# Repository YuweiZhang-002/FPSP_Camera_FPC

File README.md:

# FPSP_Camera_FPC

This repo contains FPC schematics of the newly developed FPSP camera project on an FPC board, aiming for super-high-speed parallel image processing.

## Repository Structure
| Directory | Use |
| --------- | --- |
| archive_old/ | Archived initial design (**not working**) |
| custom_fp/ | Footprint from external libraries |
| docs/ | Documentation gathered from external sources |
| camera_bringup_min/ | RP2350 firmware: OV5640 driver and PIO heartbeat |

## TODO
- [x] RP2350 Power Supply Layout
- [ ] Add Proper Power Sequencing
- [ ] Source RP2354 A4
- [ ] Source B2B Connector
- [x] B2B Connector Pinout + Layout
- [x] HSTX Layout

## 12/12/2025 PCB ordering notes

- order FR-4 board with SMT assembly, run thru **functionality tests**
- order FPC without SMT assembly, test the **FPC characteristics and stiffener position**
- RP2345A and ICM45686 IMU ordered separately to test the functionality. Once it passes the prototype test, order at JLCPCB via **global sourcing** and prep for next assembly

### TODO
 - [x] Place JLCPCB order
 - [ ] functionality test, FR4 prototype
 - [ ] functionality test, FPC stiffener position
------ 
 - [ ] sourcing RP2345A
 - [ ] sourcing ICM45686
 - [ ] sourcing board-to-board connectors from Molex 

## Firmware

Camera (OV5640) bring-up firmware for the Raspberry Pi RP2350 (pico2 board).

### Build

Standard Raspberry Pi Pico SDK CMake project. Open it with the
**Raspberry Pi Pico** VS Code extension, or configure manually:

```sh
cmake -B build -G Ninja
cmake --build build
```

Target platform: `rp2350` / board `pico2` (set in `CMakeLists.txt`).

Key files: `main.c`, `camera_bringup_min/` (OV5640 driver + PIO heartbeat),
`CMakeLists.txt`, `pico_sdk_import.cmake`.

### Firmware dependencies

Depends on the [Raspberry Pi Pico SDK](https://github.com/raspberrypi/pico-sdk)
(v2.2.0), licensed under BSD-3-Clause. The SDK is **not** included in this
repository — install it via the Pico VS Code extension or set the
`PICO_SDK_PATH` environment variable to your local SDK checkout.

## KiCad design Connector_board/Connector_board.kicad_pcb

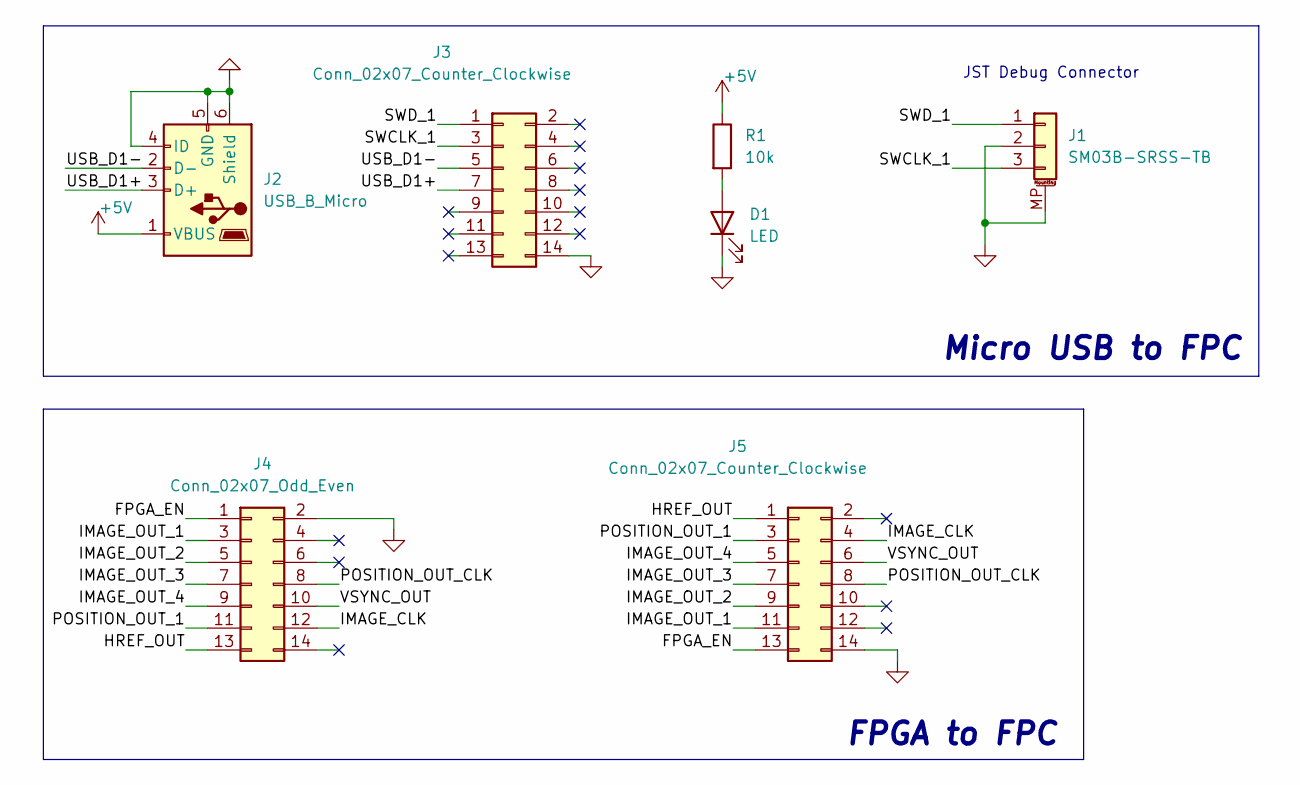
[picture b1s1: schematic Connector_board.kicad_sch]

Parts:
D1: LED; D_0603_1608Metric
J1: SM03B-SRSS-TB; JST_SH_SM03B-SRSS-TB_1x03-1MP_P1.00mm_Horizontal
J2: USB_B_Micro; USB_Micro-B_Molex_47346-0001
J3, J5: Conn_02x07_Counter_Clockwise; Molex_SlimStack_502430-1410_2x07_P0.40mm_Vertical
J4: Conn_02x07_Odd_Even; PinHeader_2x07_P2.54mm_Vertical
R1: 10k; R_0603_1608Metric_Pad0.98x0.95mm_HandSolder

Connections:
+5V: J2.1 (VBUS), R1.1
/FPGA_EN: J4.1, J5.13
/HREF_OUT: J4.13, J5.1
/IMAGE_CLK: J4.12, J5.4
/IMAGE_OUT_1: J4.3, J5.11
/IMAGE_OUT_2: J4.5, J5.9
/IMAGE_OUT_3: J4.7, J5.7
/IMAGE_OUT_4: J4.9, J5.5
/POSITION_OUT_1: J4.11, J5.3
/POSITION_OUT_CLK: J4.8, J5.8
/SWCLK_1: J1.3, J3.3
/SWD_1: J1.1, J3.1
/USB_D1+: J2.3 (D+), J3.7
/USB_D1-: J2.2 (D-), J3.5
/VSYNC_OUT: J4.10, J5.6
GND: D1.1 (K), J1.2, J1.MP (MountPin), J2.4 (ID), J2.5 (GND), J2.6 (Shield), J3.14, J3.15, J4.2, J5.14, J5.15
unnamed: D1.2 (A), R1.2

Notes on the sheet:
FPGA to FPC
Micro USB to FPC
JST Debug Connector

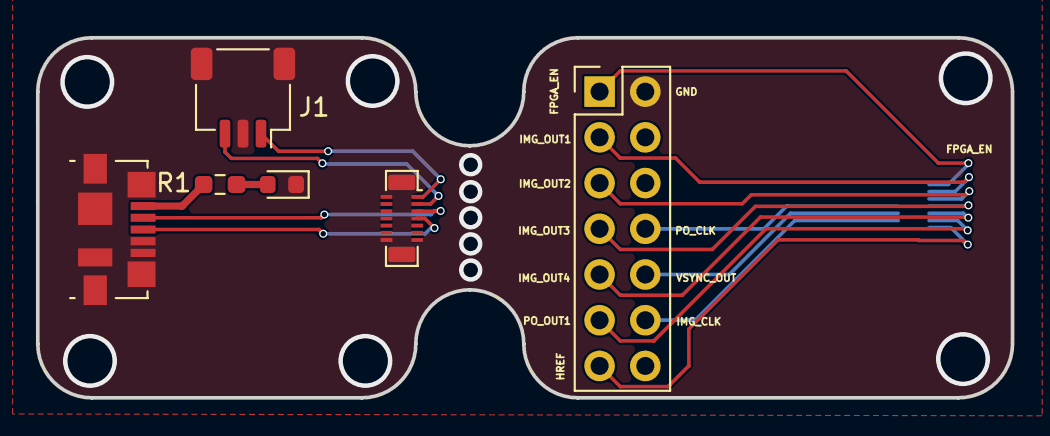
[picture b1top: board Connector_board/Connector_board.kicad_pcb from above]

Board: 2 copper layers, 54.2 x 20.0 mm, 7 parts (1 on the bottom side), 17 nets.

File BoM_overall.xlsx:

Part Name | Series Number / Description | Quantity | Source | Unit Price (GBP) | Order Code / Mouser No | Link
USB_B_Micro | USB_Micro-B_Molex_47346-0001 | 5 | Farnell | 1.2 | 1568026 | https://uk.farnell.com/molex/47346-0001/micro-usb-conn-2-0-t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
Conn_02x04_Counter_Clockwise | Molex_SlimStack_502430-0822_2x04_P0.40mm_Vertical | 5 | Mouser | 0.52 | 538-50243-00822 | https://www.mouser.co.uk/ProductDetail/Molex/502430-0822?qs=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
Conn_02x07_Counter_Clockwise | Molex_SlimStack_502430-1430_2x07_P0.40mm_Vertical | 10 | Farnell | 0.46500000000000002 | 3911710 | https://uk.farnell.com/molex/502430-1430/mezzanine-conn-hdr-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
Conn_02x04_Counter_Clockwise | Molex_SlimStack_502426-0812_2x04_P0.40mm_Vertical | 5 | Mouser | 0.55000000000000004 | 538-50242-60812 | https://www.mouser.co.uk/ProductDetail/Molex/502426-0812?qs=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
Conn_02x07_Counter_Clockwise | Molex_SlimStack_502426-1430_2x07_P0.40mm_Vertical | 10 | Farnell | 0.86799999999999999 | 3500584 | https://uk.farnell.com/molex/502426-1430/mezzanine-conn-rcpt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
SM03B-SRSS-TB | JST_SH_SM03B-SRSS-TB_1x03-1MP_P1.00mm_Horizontal | 5 | Farnell | 0.52 | 1679118 | https://uk.farnell.com/jst-japan-solderless-terminals/sm03b-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
IMU | ICM-45686 | 5 | Farnell | 7.8840000000000003 | 4572492 | https://uk.farnell.com/tdk/icm-45686/mems-module-6-axis-1-71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
LDO | TLV73315PDRV | 5 | Mouser | 0.44 | 595-TLV73315PQDRVRQ1 | https://www.mouser.co.uk/ProductDetail/Texas-Instruments/TLV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
MCU | RP2354A | 5 | Mouser | 0.751 | 358-SC151113 | https://www.mouser.co.uk/ProductDetail/Raspberry-Pi/SC151113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
Mems | SiT8008BI-13-33E-12.000000G | 5 | Mouser | 0.72099999999999997 | 788-8008BI1333E12G | https://www.mouser.co.uk/ProductDetail/SiTime/SiT8008BI-13-3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
FPC socket | molex 52435-2471 | 10 | Farnell | 2.3519999999999999 | 2396220 | https://uk.farnell.com/molex/52435-2471/connector-ffc-fpc-24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
Camera | OV5640 - 24pin fpc | 2 | Ali | N/A | N/A | https://www.aliexpress.com/p/tesla-landing/index.html?UTABTe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
2.54mm pin header: from UCL
0603 R&C: from UCL

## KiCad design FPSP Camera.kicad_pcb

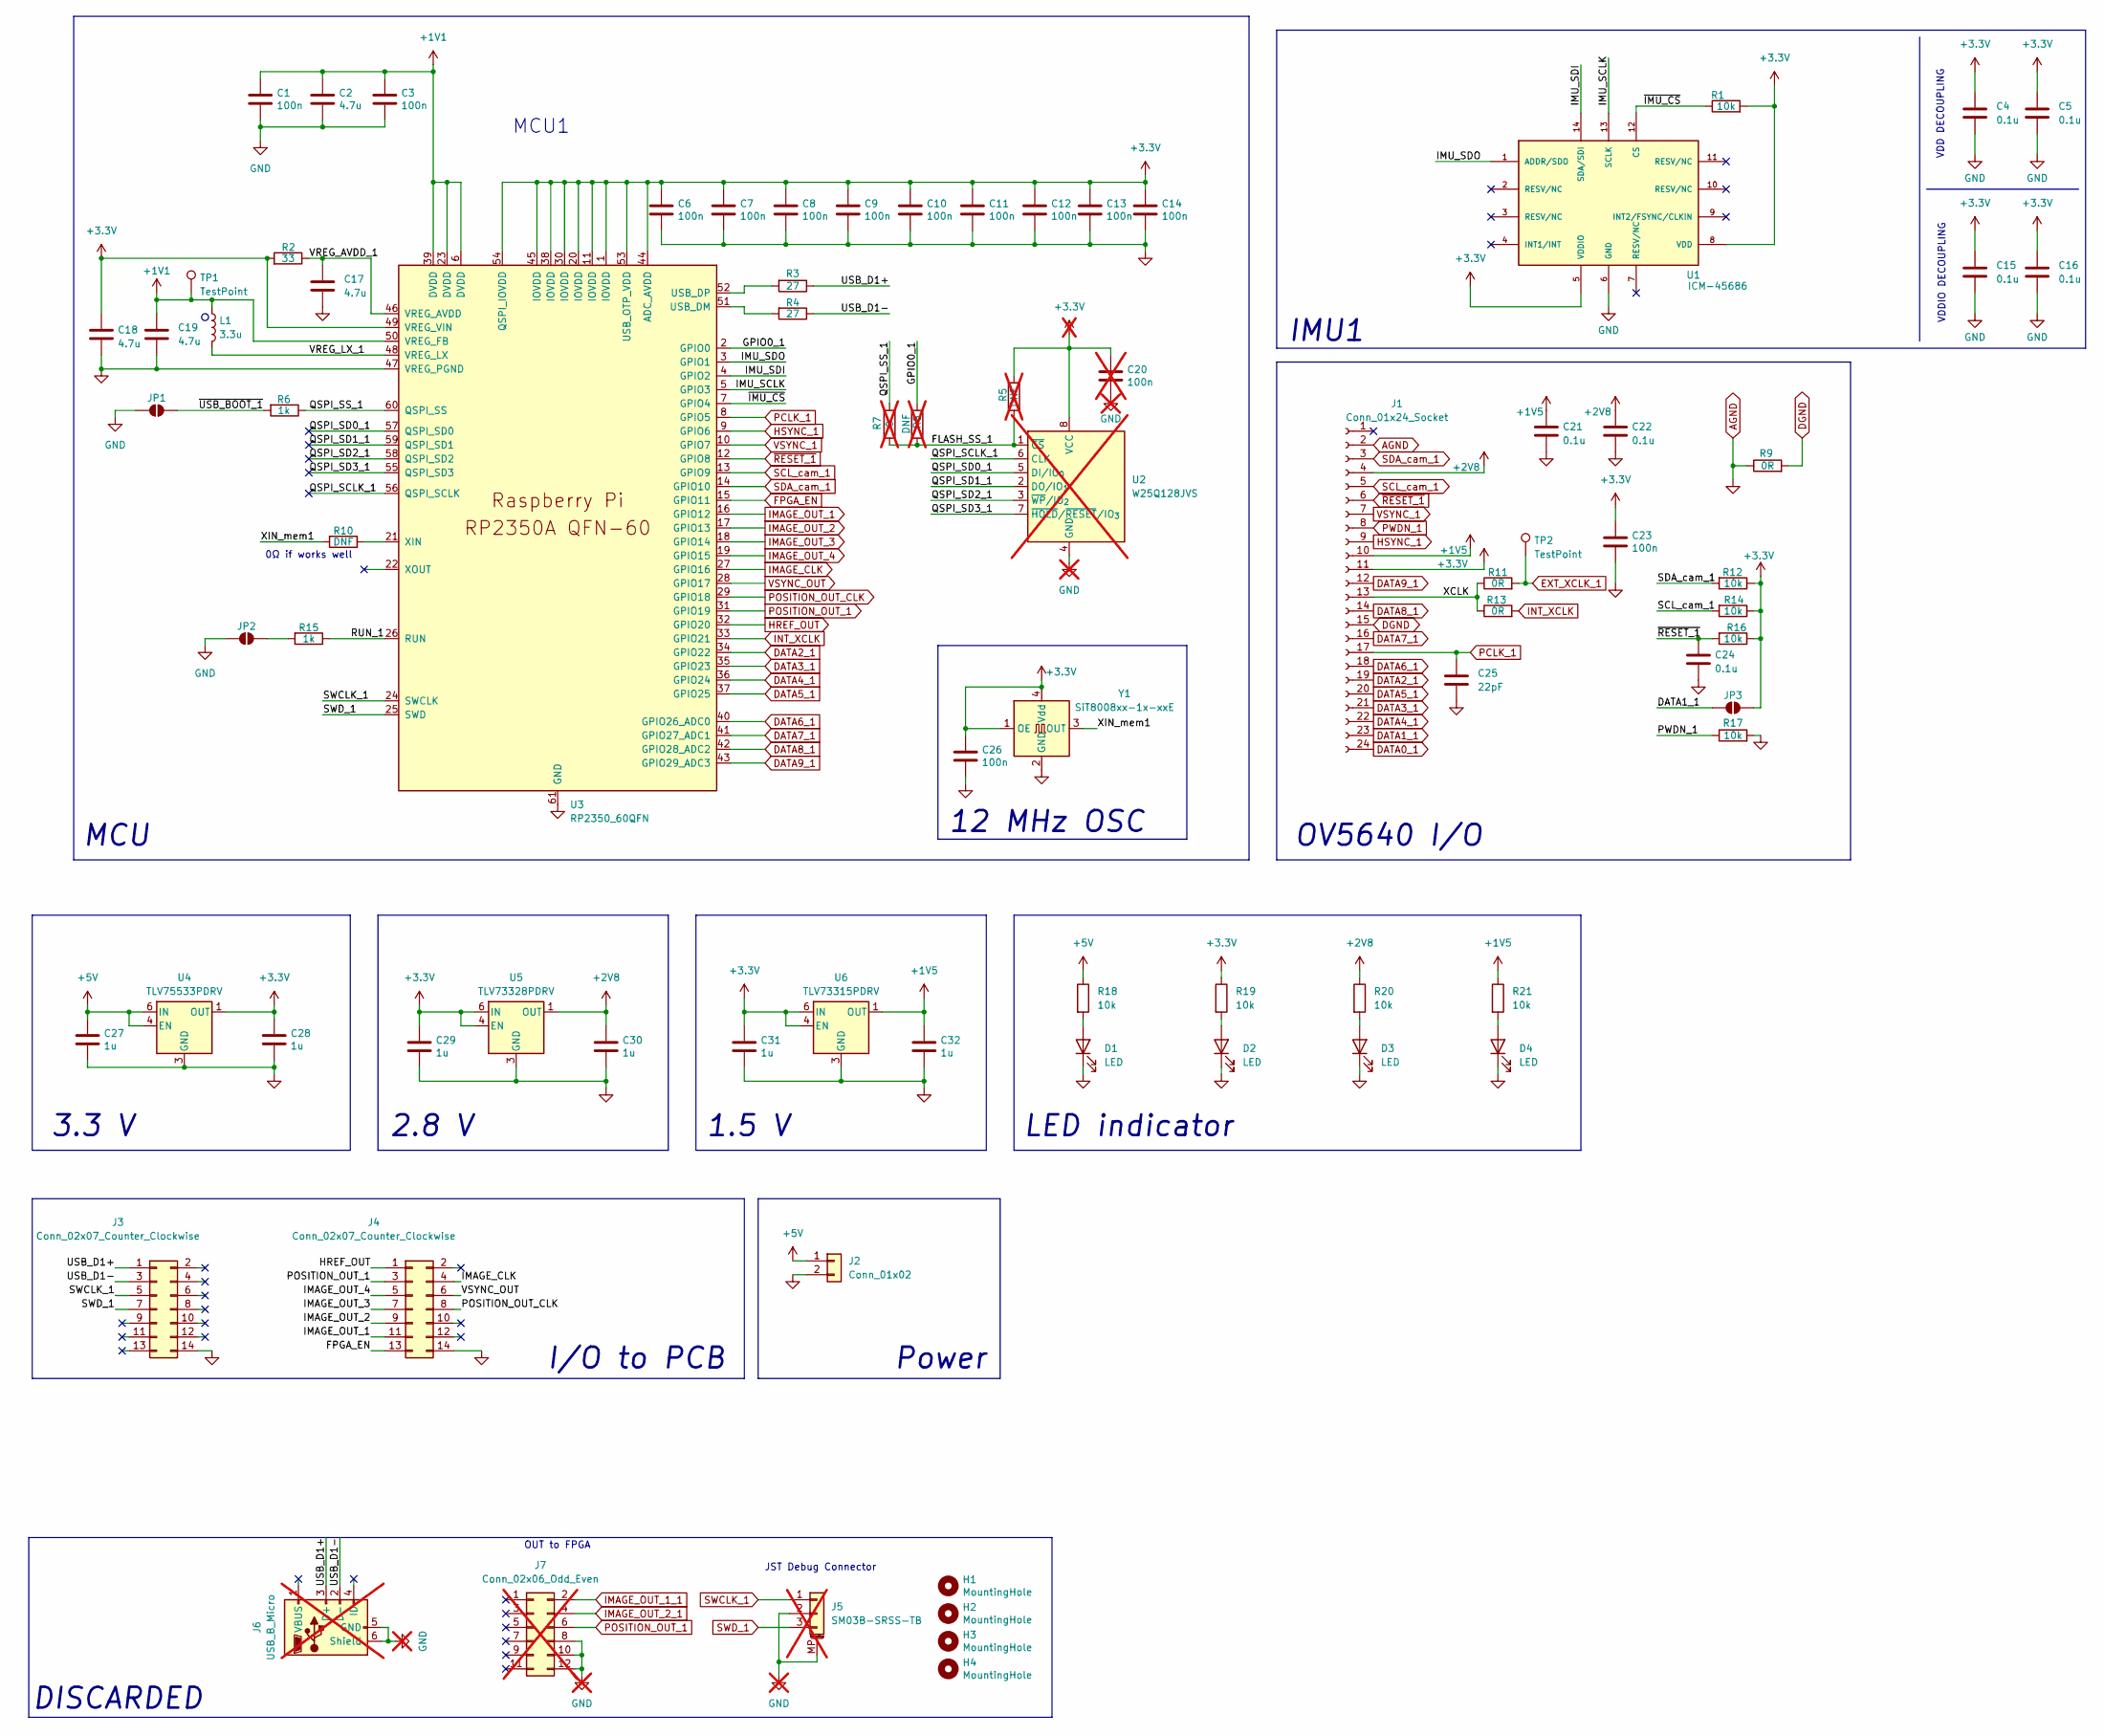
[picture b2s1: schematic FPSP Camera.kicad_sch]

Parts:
C1, C3, C6, C7, C8, C9, C10, C11, C12, C13, C14, C23, C26: 100n; C_0402_1005Metric
C2, C17, C18, C19: 4.7u; C_0402_1005Metric
C4, C5, C15, C16, C21, C22, C24: 0.1u; C_0402_1005Metric
C20: 100n; C_0603_1608Metric_Pad1.08x0.95mm_HandSolder; not fitted
C25: 22pF; C_0402_1005Metric
C27, C28, C29, C30, C31, C32: 1u; C_0402_1005Metric
D1, D2, D3, D4: LED; D_0603_1608Metric
H1, H2, H3, H4: MountingHole; MountingHole_2.7mm_M2.5
J1: Conn_01x24_Socket; MOLEX_52435-2471
J2: Conn_01x02; PinHeader_1x02_P2.54mm_Vertical
J3, J4: Conn_02x07_Counter_Clockwise; Molex_SlimStack_502426-1410_2x07_P0.40mm_Vertical
J5: SM03B-SRSS-TB; JST_SH_SM03B-SRSS-TB_1x03-1MP_P1.00mm_Horizontal; not fitted
J6: USB_B_Micro; USB_Micro-B_Amphenol_10103594-0001LF_Horizontal_modified; not fitted
J7: Conn_02x06_Odd_Even; PinHeader_2x06_P2.54mm_Vertical; not fitted
JP1, JP2, JP3: SolderJumper_2_Open; SolderJumper-2_P1.3mm_Open_RoundedPad1.0x1.5mm
L1: 3.3u; L_pol_2016
R1: 10k; R_0402_1005Metric_Pad0.72x0.64mm_HandSolder
R2: 33; R_0402_1005Metric
R3, R4: 27; R_0402_1005Metric
R5, R8: DNF; R_0603_1608Metric_Pad0.98x0.95mm_HandSolder; not fitted
R6, R15: 1k; R_0402_1005Metric
R7: 0; R_0603_1608Metric_Pad0.98x0.95mm_HandSolder; not fitted
R9, R11, R13: 0R; R_0402_1005Metric
R10: DNF; R_0402_1005Metric
R12, R14, R16, R17, R18, R19, R20, R21: 10k; R_0402_1005Metric
TP1, TP2: TestPoint; TestPoint_Pad_D1.0mm
U1: ICM-45686; IC_ICM-45686; PARTREV 0.2
U2: W25Q128JVS; SOIC-8_5.3x5.3mm_P1.27mm; not fitted
U3: RP2350_60QFN; RP2350-QFN-60-1EP_7x7_P0.4mm_EP3.4x3.4mm_ThermalVias
U4: TLV75533PDRV; WSON-6-1EP_2x2mm_P0.65mm_EP1x1.6mm
U5: TLV73328PDRV; WSON-6-1EP_2x2mm_P0.65mm_EP1x1.6mm
U6: TLV73315PDRV; WSON-6-1EP_2x2mm_P0.65mm_EP1x1.6mm
Y1: SiT8008xx-1x-xxE; Oscillator_SMD_SiT_PQFN-4Pin_2.5x2.0mm

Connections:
+1V1: C1.1, C2.1, C3.1, C19.1, L1.1, TP1.1 (1_1), U3.6 (DVDD), U3.23 (DVDD), U3.39 (DVDD), U3.50 (VREG_FB)
+1V5: C21.1, C32.1, J1.10, R21.1, U6.1 (OUT)
+2V8: C22.1, C30.1, J1.4, R20.1, U5.1 (OUT)
+3.3V: C4.1, C5.1, C6.1, C7.1, C8.1, C9.1, C10.1, C11.1, C12.1, C13.1, C14.1, C15.1, C16.1, C18.1, C20.1, C23.1, C26.1, C28.1, C29.1, C31.1, J1.11, JP3.2 (B), R1.2, R2.2, R5.1, R12.1, R14.1, R16.1, R19.1, U1.5 (VDDIO), U1.8 (VDD), U2.8 (VCC), U3.1 (IOVDD), U3.11 (IOVDD), U3.20 (IOVDD), U3.30 (IOVDD), U3.38 (IOVDD), U3.44 (ADC_AVDD), U3.45 (IOVDD), U3.49 (VREG_VIN), U3.53 (USB_OTP_VDD), U3.54 (QSPI_IOVDD), U4.1 (OUT), U5.4 (EN), U5.6 (IN), U6.4 (EN), U6.6 (IN), Y1.1 (OE), Y1.4 (Vdd)
+5V: C27.1, J2.1, R18.1, U4.4 (EN), U4.6 (IN)
/GPIO0_1: R8.2, U3.2 (GPIO0)
/IMU_SCLK: U1.13 (SCLK), U3.5 (GPIO3)
/IMU_SDI: U1.14 (SDA/SDI), U3.4 (GPIO2)
/IMU_SDO: U1.1 (ADDR/SDO), U3.3 (GPIO1)
/QSPI_SCLK_1: U2.6 (CLK), U3.56 (QSPI_SCLK)
/QSPI_SD0_1: U2.5 (DI/IO_{0}), U3.57 (QSPI_SD0)
/QSPI_SD1_1: U2.2 (DO/IO_{1}), U3.59 (QSPI_SD1)
/QSPI_SD2_1: U2.3 (~WP/IO_{2}), U3.58 (QSPI_SD2)
/QSPI_SD3_1: U2.7 (~HOLD/~RESET/IO_{3}), U3.55 (QSPI_SD3)
/QSPI_SS_1: R6.1, R7.2, U3.60 (QSPI_SS)
/RUN_1: R15.1, U3.26 (RUN)
/USB_D1+: J3.1, J6.3 (D+), R3.1
/USB_D1-: J3.3, J6.2 (D-), R4.1
/VREG_AVDD_1: C17.1, R2.1, U3.46 (VREG_AVDD)
/VREG_LX_1: L1.2, U3.48 (VREG_LX)
/XCLK: J1.13, R11.1, R13.1
/XIN_mem1: R10.2, Y1.3 (OUT)
/~IMU_CS: R1.1, U1.12 (CS), U3.7 (GPIO4)
/~USB_BOOT_1: JP1.2 (B), R6.2
AGND: C1.2, C2.2, C3.2, C4.2, C5.2, C6.2, C7.2, C8.2, C9.2, C10.2, C11.2, C12.2, C13.2, C14.2, C15.2, C16.2, C17.2, C18.2, C19.2, C20.2, C21.2, C22.2, C23.2, C24.2, C25.2, C26.2, C27.2, C28.2, C29.2, C30.2, C31.2, C32.2, D1.1 (K), D2.1 (K), D3.1 (K), D4.1 (K), J1.2, J1.MP, J2.2, J3.14, J3.15, J3.16, J4.14, J4.15, J4.16, J5.2, J5.MP (MountPin), J6.5 (GND), J6.6 (Shield), J7.8, J7.10, J7.12, JP1.1 (A), JP2.1 (A), R9.1, R17.2, U1.6 (GND), U2.4 (GND), U3.47 (VREG_PGND), U3.61 (GND), U4.3 (GND), U4.7 (GND), U5.3 (GND), U5.7 (GND), U6.3 (GND), U6.7 (GND), Y1.2 (GND)
DATA0_1: J1.24
DATA1_1: J1.23, JP3.1 (A)
DATA2_1: J1.19, U3.34 (GPIO22)
DATA3_1: J1.21, U3.35 (GPIO23)
DATA4_1: J1.22, U3.36 (GPIO24)
DATA5_1: J1.20, U3.37 (GPIO25)
DATA6_1: J1.18, U3.40 (GPIO26_ADC0)
DATA7_1: J1.16, U3.41 (GPIO27_ADC1)
DATA8_1: J1.14, U3.42 (GPIO28_ADC2)
DATA9_1: J1.12, U3.43 (GPIO29_ADC3)
DGND: J1.15, R9.2
EXT_XCLK_1: R11.2, TP2.1 (1_1)
FPGA_EN: J4.13, U3.15 (GPIO11)
HREF_OUT: J4.1, U3.32 (GPIO20)
HSYNC_1: J1.9, U3.9 (GPIO6)
IMAGE_CLK: J4.4, U3.27 (GPIO16)
IMAGE_OUT_1: J4.11, U3.16 (GPIO12)
IMAGE_OUT_2: J4.9, U3.17 (GPIO13)
IMAGE_OUT_3: J4.7, U3.18 (GPIO14)
IMAGE_OUT_4: J4.5, U3.19 (GPIO15)
INT_XCLK: R13.2, U3.33 (GPIO21)
unnamed: D1.2 (A), R18.2
unnamed: D2.2 (A), R19.2
unnamed: D3.2 (A), R20.2
unnamed: D4.2 (A), R21.2
unnamed: JP2.2 (B), R15.2
unnamed: R5.2, R7.1, R8.1, U2.1 (~CS)
unnamed: R4.2, U3.51 (USB_DM)
unnamed: R3.2, U3.52 (USB_DP)
unnamed: R10.1, U3.21 (XIN)
PCLK_1: C25.1, J1.17, U3.8 (GPIO5)
POSITION_OUT_1: J4.3, J7.6, U3.31 (GPIO19)
POSITION_OUT_CLK: J4.8, U3.29 (GPIO18)
PWDN_1: J1.8, R17.1
SCL_cam_1: J1.5, R14.2, U3.13 (GPIO9)
SDA_cam_1: J1.3, R12.2, U3.14 (GPIO10)
SWCLK_1: J3.5, U3.24 (SWCLK)
SWD_1: J3.7, U3.25 (SWD)
VSYNC_1: J1.7, U3.10 (GPIO7)
VSYNC_OUT: J4.6, U3.28 (GPIO17)
~RESET_1: C24.1, J1.6, R16.2, U3.12 (GPIO8)

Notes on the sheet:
I/O to PCB
0Ω if works well
IMU1
3.3 V
MCU
MCU1
12 MHz OSC
Power
2.8 V
VDD DECOUPLING
LED indicator
1.5 V
VDDIO DECOUPLING
OV5640 I/O
DISCARDED
JST Debug Connector
OUT to FPGA

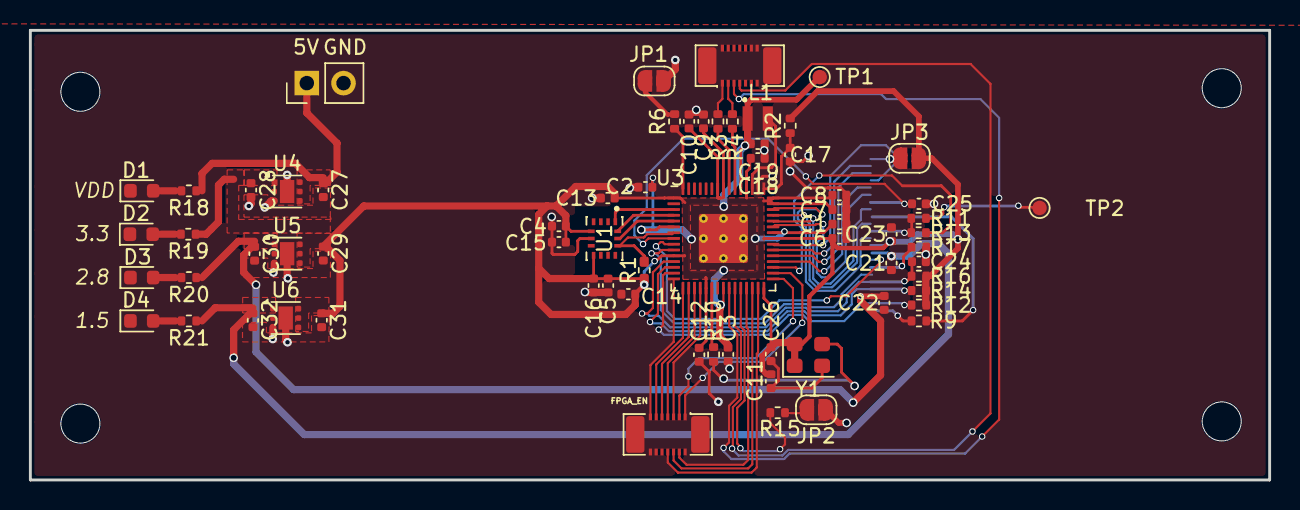
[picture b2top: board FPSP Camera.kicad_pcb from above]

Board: 4 copper layers, 85.7 x 31.1 mm, 73 parts (1 on the bottom side), 58 nets.

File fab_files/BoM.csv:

"Comment","Designator","Footprint","LCSC Part Number","Qty","DNP","Exclude from BOM","Exclude from Board"
"0.1u","C1,C2,C15,C16,C21,C22,C23","Capacitor_SMD:C_0402_1005Metric","C60474","7","","",""
"100n","C3,C5,C6,C7,C8,C9,C10,C11,C12,C13,C14,C25,C32","Capacitor_SMD:C_0402_1005Metric","C60474","13","","",""
"4.7u","C4,C17,C18,C19","Capacitor_SMD:C_0402_1005Metric","C106859","4","","",""
"100n","C20","Capacitor_SMD:C_0603_1608Metric_Pad1.08x0.95mm_HandSolder","N/A","1","DNP","","Excluded from board"
"22pF","C24","Capacitor_SMD:C_0402_1005Metric","C106203","1","","",""
"1u","C26,C27,C28,C29,C30,C31","Capacitor_SMD:C_0402_1005Metric","C106253","6","","",""
"LED","D1,D2,D3,D4","Diode_SMD:D_0603_1608Metric","C2286","4","","",""
"MountingHole","H1,H2,H3,H4","MountingHole:MountingHole_2.7mm_M2.5","N/A","4","","",""
"Conn_01x24_Socket","J1","Connector_FFC-FPC:TE_2-1734839-3_1x23-1MP_P0.5mm_Horizontal","C6668214","1","","",""
"Conn_02x04_Counter_Clockwise","J2","Connector_Molex:Molex_SlimStack_502426-0810_2x04_P0.40mm_Vertical","C563931","1","","",""
"Conn_02x07_Counter_Clockwise","J3","Connector_Molex:Molex_SlimStack_502426-1410_2x07_P0.40mm_Vertical","C563932","1","","",""
"SM03B-SRSS-TB","J4","Connector_JST:JST_SH_SM03B-SRSS-TB_1x03-1MP_P1.00mm_Horizontal","N/A","1","DNP","","Excluded from board"
"USB_B_Micro","J5","RP2350_60QFN_minimal:USB_Micro-B_Amphenol_10103594-0001LF_Horizontal_modified","N/A","1","DNP","","Excluded from board"
"Conn_02x06_Odd_Even","J6","Connector_PinHeader_2.54mm:PinHeader_2x06_P2.54mm_Vertical","N/A","1","DNP","","Excluded from board"
"Conn_01x02","J7","Connector_PinHeader_2.54mm:PinHeader_1x02_P2.54mm_Vertical","N/A","1","","",""
"SolderJumper_2_Open","JP1,JP2,JP3","Jumper:SolderJumper-2_P1.3mm_Open_RoundedPad1.0x1.5mm","N/A","3","","Excluded from BOM",""
"3.3u","L1","Inductor_SMD:L_pol_2016","N/A","1","","",""
"10k","R1","Resistor_SMD:R_0402_1005Metric_Pad0.72x0.64mm_HandSolder","C60489","1","","",""
"33","R2","Resistor_SMD:R_0402_1005Metric","C15011","1","","",""
"27","R3,R4","Resistor_SMD:R_0402_1005Metric","C15011","2","","",""
"DNF","R5,R8","Resistor_SMD:R_0603_1608Metric_Pad0.98x0.95mm_HandSolder","N/A","2","DNP","","Excluded from board"
"1k","R6,R15","Resistor_SMD:R_0402_1005Metric","C105637","2","","",""
"0","R7","Resistor_SMD:R_0603_1608Metric_Pad0.98x0.95mm_HandSolder","N/A","1","DNP","","Excluded from board"
"0R","R9,R11,R13","Resistor_SMD:R_0402_1005Metric","C60485","3","","",""
"DNF","R10","Resistor_SMD:R_0402_1005Metric","N/A","1","","",""
"10k","R12,R14,R16,R17,R18,R19,R20,R21","Resistor_SMD:R_0402_1005Metric","C60489","8","","",""
"TestPoint","TP1","TestPoint:TestPoint_Pad_D1.0mm","N/A","1","","",""
"ICM-45686","U1","ICM_45686:IC_ICM-45686","N/A","1","","",""
"W25Q128JVS","U2","Package_SO:SOIC-8_5.3x5.3mm_P1.27mm","N/A","1","DNP","","Excluded from board"
"RP2354A_60QFN","U3","projLib:RP2350-QFN-60-1EP_7x7_P0.4mm_EP3.4x3.4mm_ThermalVias","C41378174","1","","",""
"TLV75533PDRV","U4","Package_SON:WSON-6-1EP_2x2mm_P0.65mm_EP1x1.6mm","C2861750","1","","",""
"TLV73328PDRV","U5","Package_SON:WSON-6-1EP_2x2mm_P0.65mm_EP1x1.6mm","N/A","1","","",""
"TLV73315PDRV","U6","Package_SON:WSON-6-1EP_2x2mm_P0.65mm_EP1x1.6mm","N/A","1","","",""
"SiT8008xx-1x-xxE","Y1","Oscillator:Oscillator_SMD_SiT_PQFN-4Pin_2.5x2.0mm","C347962","1","","",""

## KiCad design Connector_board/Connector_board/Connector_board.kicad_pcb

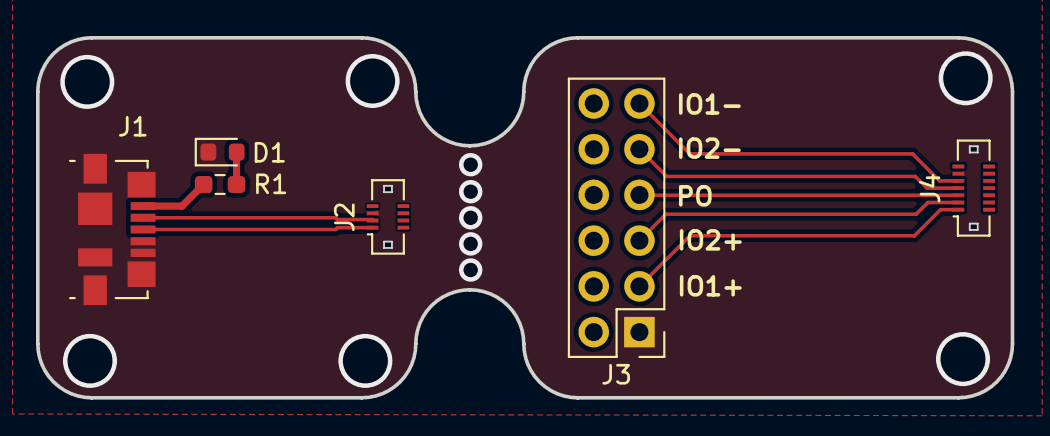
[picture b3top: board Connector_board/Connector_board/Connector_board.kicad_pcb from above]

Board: 2 copper layers, 54.2 x 20.0 mm, 6 parts (0 on the bottom side), 10 nets.

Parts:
D1: LED; D_0603_1608Metric
J1: USB_B_Micro; USB_Micro-B_Molex_47346-0001
J2: Conn_02x04_Counter_Clockwise; Molex_SlimStack_502430-0820_2x04_P0.40mm_Vertical
J3: Conn_02x06_Counter_Clockwise; PinHeader_2x06_P2.54mm_Vertical
J4: Conn_02x07_Counter_Clockwise; Molex_SlimStack_502430-1410_2x07_P0.40mm_Vertical
R1: 10k; R_0603_1608Metric_Pad0.98x0.95mm_HandSolder

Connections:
+3V3: J1.1 (VBUS), R1.1
/IMAGE_OUT_1_1+: J3.3, J4.1
/IMAGE_OUT_1_1-: J3.11, J4.9
/IMAGE_OUT_2_1+: J3.5, J4.3
/IMAGE_OUT_2_1-: J3.9, J4.7
/POSITION_OUT_1: J3.7, J4.5
/USB_D1+: J1.3 (D+), J2.1
/USB_D1-: J1.2 (D-), J2.3
GND: D1.1 (K), J1.4 (ID), J1.5 (GND), J1.6 (Shield), J2.5, J3.1, J4.11
unnamed: D1.2 (A), R1.2

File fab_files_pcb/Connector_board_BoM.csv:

Reference,Qty,Value,DNP,Exclude from BOM,Exclude from Board,Footprint,Datasheet
D1,1,LED,,,,Diode_SMD:D_0603_1608Metric,~
J1,1,USB_B_Micro,,,,Connector_USB:USB_Micro-B_Molex_47346-0001,~
J2,1,Conn_02x04_Counter_Clockwise,,,,Connector_Molex:Molex_SlimStack_502430-0820_2x04_P0.40mm_Vertical,~
J3,1,Conn_02x06_Counter_Clockwise,,,,Connector_PinHeader_2.54mm:PinHeader_2x06_P2.54mm_Vertical,~
J4,1,Conn_02x07_Counter_Clockwise,,,,Connector_Molex:Molex_SlimStack_502430-1410_2x07_P0.40mm_Vertical,~
J5,1,SM03B-SRSS-TB,,,,Connector_JST:JST_SH_SM03B-SRSS-TB_1x03-1MP_P1.00mm_Horizontal,~
R1,1,10k,,,,Resistor_SMD:R_0603_1608Metric_Pad0.98x0.95mm_HandSolder,~

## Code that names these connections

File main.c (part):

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 *  工程模块化：
 *      - heartbeat.pio       : PIO 单引脚心跳 (验证 RP2354 + PIO)
 *      - ov5640.c / ov5640.h : SCCB 驱动 + RGB565/DVP 配置 + color bar
 *      - main.c              : XCLK / GPIO / 主循环
 *
 *  约束 (按用户要求)：
 *      - 不使用 DMA
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 *      HEARTBEAT_PIN : GP5, 空闲脚。本板无 GPIO 用户 LED (D1~D4 为电源指示灯),
 *                      此脚仅作示波器 / 外接 LED 观测点, 不占用相机数据线。
 * --------------------------------------------------------------------------- */
#define CAM_PIN_XCLK         26u   /* INT_XCLK (PWM 输出) */
#define CAM_PIN_VSYNC         7u   /* 单端 VSYNC */
#define CAM_PIN_HREF         16u   /* 单端 HSYNC */
#define CAM_PIN_PCLK         27u   /* 单端 PCLK */

#define CAM_PIN_D0_P         15u   /* IMAGE_OUT_1 正极 */
#define CAM_PIN_D0_N         12u   /* IMAGE_OUT_1 负极 */
#define CAM_PIN_D1_P         14u   /* IMAGE_OUT_2 正极 */
#define CAM_PIN_D1_N         13u   /* IMAGE_OUT_2 负极 */

#define HEARTBEAT_PIN         5u   /* 空闲脚 (本板无板载 LED) */

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
    /* ----- 2) 给 OV5640 提供 XCLK ---------------------------------- */
    xclk_init_pwm_approx_24mhz();
    printf("[boot] XCLK PWM on GP%u (~24 MHz)\n", CAM_PIN_XCLK);

    /* ----- 3) 准备相机信号 GPIO 为输入 ----------------------------- */
    camera_signal_gpio_init();
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
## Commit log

2025-11-30 connector PCB added
2025-11-30 clean up
2025-11-30 Sch cleanup
2025-11-30 Connector board tweaked
2025-11-30 routing updates
2025-11-30 pin assignment done
2025-11-30 finished connecting all data pins
2025-12-01 layout finalized (?)
2025-12-01 connector board updated
2025-12-01 minor changes
2025-12-04 minor fixes
2025-12-08 doc -> pdf updated
2025-12-10 minor changes in stiffener layers
2025-12-10 change default clearance, add fabrication files
2025-12-10 tweak gitignore, add BoM and CPL
2025-12-11 manufacturing file for PCB added
2025-12-11 update gerber
2025-12-12 cleanup
2025-12-12 add todo before JLCPCB ordering
2025-12-12 update FR4 version
2025-12-12 FPC socket foorprint replaced
2026-06-19 test PCB version 2 completed
2026-06-19 refined 5V net isolation
2026-06-19 Initial commit: FPSP camera FPC bring-up (RP2350/pico2)
2026-06-19 Stop tracking local Claude Code settings
